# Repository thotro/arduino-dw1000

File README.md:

# arduino-dw1000

A library that offers basic functionality to use Decawave's DW1000 chips/modules with Arduino
(see https://www.decawave.com/products/dwm1000-module).

Project state
-------------

**Development:**
There is **no active development** by the owner *thotro*.

This library is currently (2019) **not actively maintained**.

Anyway you can create pull requests if you found a bug or developed a new feature. They maybe help others.

**TODOs:**
* Fill wiki: https://github.com/thotro/arduino-dw1000/wiki
* MAC and frame filtering, error handling
* Sleep/power optimizations
* Refactor `DW1000Mac`
* Refactor `DW1000Ranging`
* Refactor `DW1000Device`
* Update examples (complete todos in header notice)

**What can I do with this lib?:**
Stable transmission of messages between two modules is possible. The code for device tuning is working as well, hence different modes of operation can be chosen. As frame filtering (i.e. via MAC conforming messages) is partially implemented yet, internal features of the chip for node addressing and auto-acknowledgement of messages can not be used. This is part of a future milestone. For now, if acknowledgements are required, they have to be sent manually and node addresses have to be encoded in the message payload and processed by the host controller.

**General notice:**
* The documentation https://github.com/thotro/arduino-dw1000/tree/master/extras/doc is manually generated and maybe out of date.
* Datasheet and application notices are available at https://www.decawave.com/ (require free registration).

Installation
------------

**Requires c++11 support**, Arduino IDE >= 1.6.6 support c++11.

 1. Get a ZIP file of the master branch or the latest release and save somewhere on your machine.
 2. Open your Arduino IDE and goto _Sketch_ / _Include Library_ / _Add .ZIP Library..._
 3. Select the downloaded ZIP file of the DW1000 library
 4. You should now see the library in the list and have access to the examples in the dedicated section of the IDE

Note that in version 1.6.6 of your Arduino IDE you can get the library via the Arduino library manager.

Contents
--------

 * [Project structure](../../wiki/Project-structure)
 * [Features and design intentions](../../wiki/Features)
 * [Testbed and Adapter board](../../wiki/Testbed-and-Adapter-board)
 * [Projects, Media, Links](../../wiki/Projects)
 * [Benchmarks](../../wiki/Benchmarks)
 * API docs
   * [HTML](https://cdn.rawgit.com/thotro/arduino-dw1000/master/extras/doc/html/index.html)
   * [PDF](https://cdn.rawgit.com/thotro/arduino-dw1000/master/extras/doc/DW1000_Arduino_API_doc.pdf)

Usage
-----

General usage of the DW1000 library is depicted below. Please see the Arduino test example codes (described in the [project structure](../../wiki/Project-structure)) for more up-to-date and operational reference usage. 

At the moment the library contains two types:
 * **DW1000:**
 State: stable.
 The statically accessible entity to work with your modules. Offers a variety of configuration options and manages module states and actions. 
 
 * **DW1000Time:**
 State: stable.
 Container entities that handle DW1000 specific timing values. These are required to allow accurate timestamps and time based computations; they aid in avoiding potential precision and capacity problems of standard number formats in Arduino and basically are wrapper objects for 64-bit signed integer data types; most importantly they take care of all bit-to-time-and-distance (and vice versa) conversions.
 
 * **DW1000Ranging:**
 State: prototype.
 Contain all functions which allow to make the ranging protocole. 
 
 * **DW1000Device:**
 State: prototype.
 Contain all informations (long address, short ephemeral address, DW1000Time of transition)  about a distant device (anchor or tag) on the same network.
 
 * **DW1000Mac:**
 State: prototype.
 This class is a child of the DW1000Device class and allow to generate the MAC frame for his DW1000Device parent.

```Arduino
#include <DW1000.h>
...
// init with interrupt line and optionally with reset line
DW1000.begin(irq_pin[, rst_pin]);
// select a specific chip via a chip select line
DW1000.select(cs_pin);
// or use DW1000.reselect(cs_pin) to switch to previously selected chip
...
// open a device configuration sessions
DW1000.newConfiguration();
// configure specific aspects and/or choose defaults
DW1000.setDefaults();
DW1000.setDeviceAddress(5);
DW1000.setNetworkId(10);
// modes that define data rate, frequency, etc. (see API docs)
DW1000.enableMode(DW1000.MODE_LONGDATA_RANGE_LOWPOWER);
// ... and other stuff - finally upload to the module.
DW1000.commitConfiguration();
...
// set some interrupt callback routines
DW1000.attachSentHandler(some_handler_function);
DW1000.attachReceivedHandler(another_handler_function);
...
// open a new transmit session
DW1000.newTransmit();
// configure specific aspects and/or choose defaults
DW1000.setDefaults();
DW1000.setData(some_data);
DW1000Time delayTime = DW1000Time(100, DW1000Time::MILLISECONDS);
[DW1000Time futureTimestamp = ]DW1000.setDelay(delayTime);
// ... and other stuff - finally start the transmission
DW1000.startTransmit();
...
// similar for a receiving session, like so ...
DW1000.newReceive();
DW1000.setDefaults();
// so we don't need to restart the receiver manually each time
DW1000.receivePermanently(true);
// ... and other stuff - finally start awaiting messages
DW1000.startReceive();
...
```

Dependency
----------

Disclaimer:
This is maybe a incomplete list. Please notice that some dependency libraries may **require** a **reproduction** of copyright and license, **even if they are shipped as binary!!**

* **Arduino.h**

  * From: Arduino IDE / target specific
  * License: (target: Arduino) GNU Lesser General Public License 2.1
  
* **SPI.h**

  * From: Arduino IDE / target specific
  * License: (target: Arduino) GNU Lesser General Public License 2.1
  
* **stdint.h**

  * From: Arduino IDE / Compiler and target specific
  * License: different

* **stdio.h**

  * From: Arduino IDE / Compiler and target specific
  * License: different
  
* **stdlib.h**

  * From: Arduino IDE / Compiler and target specific
  * License: different
  
* **string.h**

  * From: Arduino IDE / Compiler and target specific
  * License: different

License
-------
Apache License 2.0 (see [LICENSE.md](https://github.com/thotro/arduino-dw1000/blob/master/LICENSE.md))

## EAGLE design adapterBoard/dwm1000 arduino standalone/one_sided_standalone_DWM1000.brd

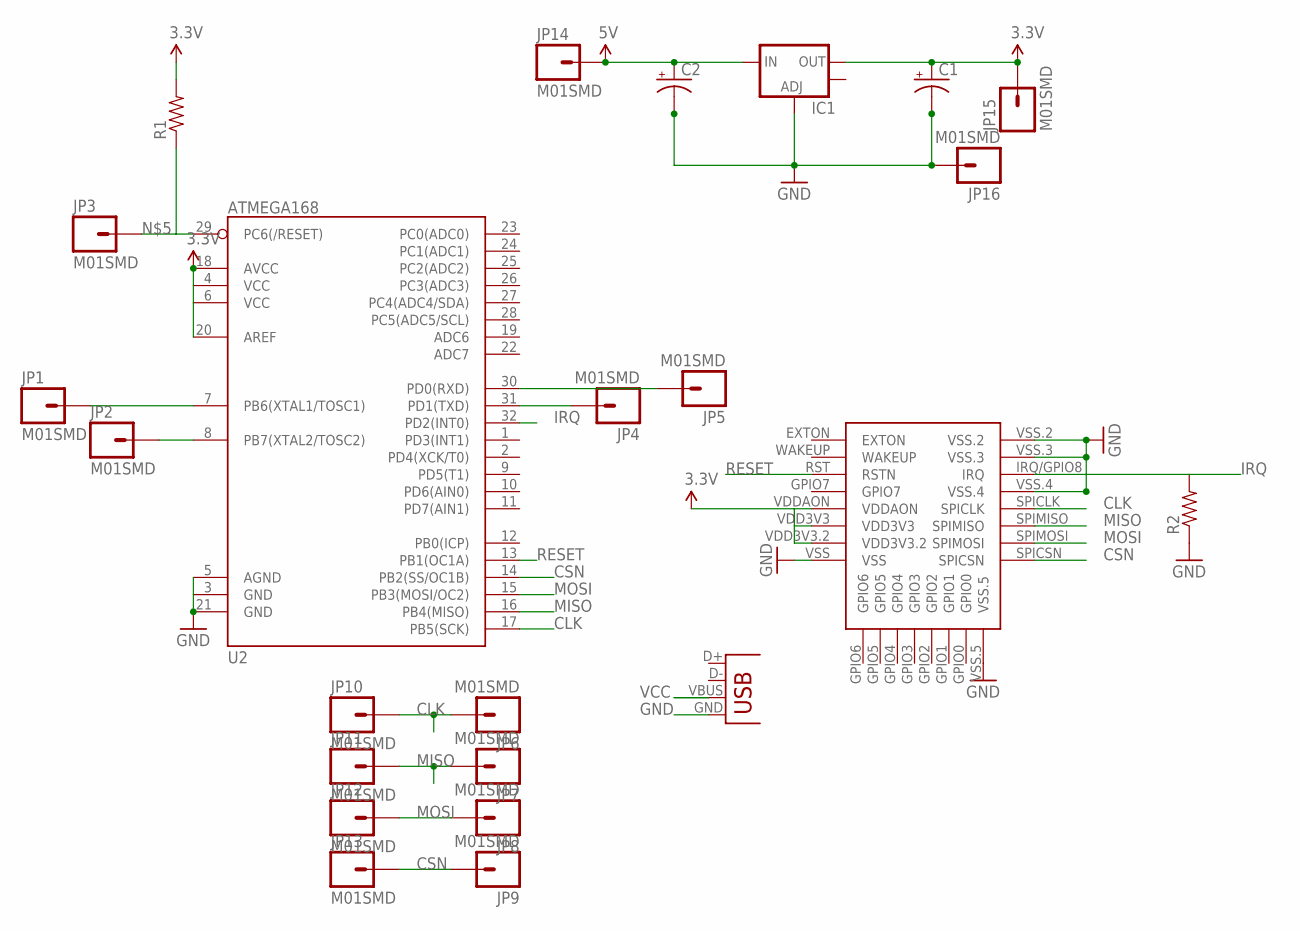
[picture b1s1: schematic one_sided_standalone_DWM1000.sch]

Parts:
C1, C2: CAP_POL3528-KIT; EIA3528-KIT
IC1: V_REG_LM1117SOT223; SOT223
JP1, JP2, JP3, JP4, JP5, JP6, JP7, JP8, JP9, JP10, JP11, JP12, JP13, JP14, JP15, JP16: M01SMD; LUXEON-PAD
R1, R2: RESISTOR0805-RES; 0805
U2: ATMEGA168; TQFP32-08
U$1: DWM1000
X1: USB-MICROB

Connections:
CLK: JP6.P$1, JP10.P$1, U2.17 (PB5(SCK)), U$1.SPICLK
CSN: JP9.P$1, JP13.P$1, U2.14 (PB2(SS/OC1B)), U$1.SPICSN
GND: C1.C (-), C2.C (-), IC1.1 (ADJ), JP16.P$1, R2.1, U2.3 (GND), U2.5 (AGND), U2.21 (GND), U$1.VSS, U$1.VSS.2, U$1.VSS.3, U$1.VSS.4, U$1.VSS.5, X1.GND
IRQ: R2.2, U2.32 (PD2(INT0)), U$1.IRQ/GPIO8 (IRQ)
MISO: JP7.P$1, JP11.P$1, U2.16 (PB4(MISO)), U$1.SPIMISO
MOSI: JP8.P$1, JP12.P$1, U2.15 (PB3(MOSI/OC2)), U$1.SPIMOSI
unnamed: JP1.P$1, U2.7 (PB6(XTAL1/TOSC1))
unnamed: JP2.P$1, U2.8 (PB7(XTAL2/TOSC2))
unnamed: JP3.P$1, R1.1, U2.29 (PC6(/RESET))
unnamed: JP4.P$1, U2.31 (PD1(TXD))
unnamed: JP5.P$1, U2.30 (PD0(RXD))
RESET: U2.13 (PB1(OC1A)), U$1.RST (RSTN)
VCC: C2.A (+), IC1.3 (IN), JP14.P$1, X1.VBUS
VCC3.3: C1.A (+), IC1.2 (OUT), JP15.P$1, R1.2, U2.6 (VCC), U2.18 (AVCC), U2.20 (AREF), U$1.VDD3V3, U$1.VDD3V3.2, U$1.VDDAON

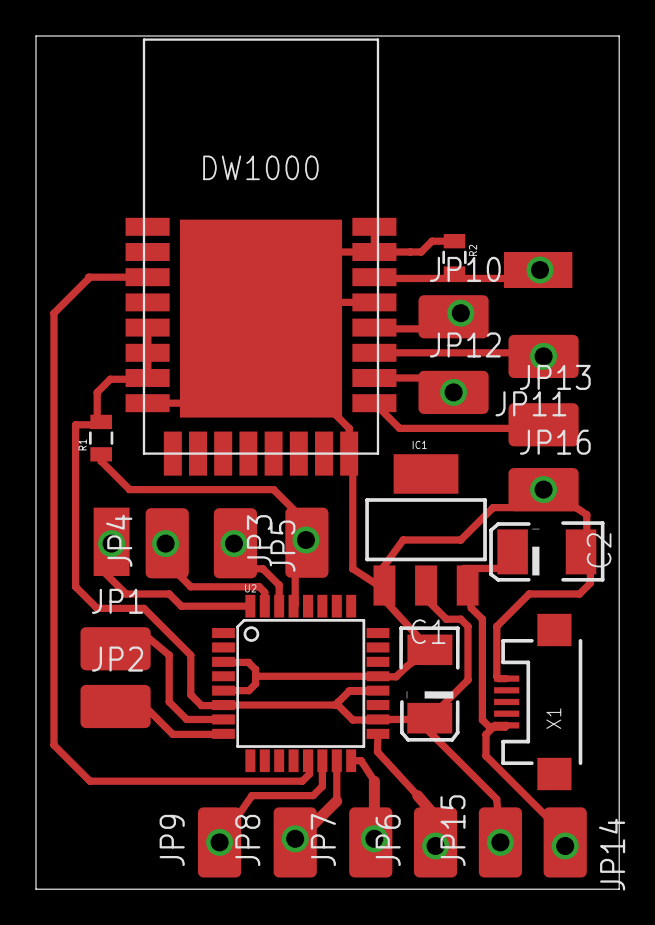
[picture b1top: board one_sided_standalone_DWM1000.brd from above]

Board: 2 copper layers, 32.4 x 47.4 mm, 24 parts (0 on the bottom side), 14 nets.

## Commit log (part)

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2015-01-22 initial arduino test code
2015-01-24 some further commands used arduino.h bit handling
2015-01-25 TX related registers, especially TX_FCTRL
2015-01-26 DEBUG/Unit code, unit test project initial commit
2015-01-26 project structure explained
2015-02-05 capture most important RX system status events
2015-02-08 adapter board for 0.1in breadboard/protoboard (first draft)
2015-03-06 first production version of adapter board
2015-04-12 pretty bit field printing, bug fixes
2015-04-15 interrupt handling, chip reset and fixes
2015-04-18 mem optimization, RX/TX tests (in progress)
2015-04-19 pretty register content printing (device debug)
2015-04-20 default configuration fixes according to spec
2015-05-17 bugfix, internal channel control and device tuning
2015-05-18 device configuration tuning
2015-05-20 Simple (Arduino-)String based RX/TX data handling
2015-05-21 stable RX/TX, bugfix mem leak
2015-05-23 Testbed description
2015-05-27 Refactored to single static object (DW1000) + infrastructure for callback handlers
2015-05-31 stability fixes + more RX callbacks
2015-06-01 Updated info
2015-06-08 ranging demo (in progress)
2015-06-13 Timestamp bugfix + first ranging results (still require testing)
2015-06-15 code cleanup
2015-06-16 soft reset + tuning code completed + bugfix in syscfg
2015-06-19 fixed wiki links
2015-06-19 fixed ping pong test
2015-06-20 minor fix and readme update
2015-06-24 bugfix chip tuning
2015-06-25 OTP and calibration (in progress)
2015-06-25 api doc (in progress), api cleanup + bugfix for tune
2015-06-26 exclude doc from stats
2015-06-30 Fixed returned future time in setDelay(..) (antenna delay compensation)
2015-07-03 device mode printing + some progress on ranging
2015-07-04 progress on API docs
2015-07-06 changed to more permissive Apache License + Arduino conforming library format (1.5)
2015-07-06 specified and tagged v0.5, as Arduino conforming library
2015-07-06 bugfix SPI, enableClock order (thanks Ankit)
2015-07-07 bugfix preamble code + first path signal strength read-back
2015-07-07 fixed broken links to API docs
2015-07-14 Gerber files for adapter board
2015-07-17 receive power level + dBm correction
2015-07-18 smart tx power management
2015-07-21 bugfix in 110kbps tuning
2015-07-25 Apache license for all examples
2015-07-31 allow shorter replyDelay
    - decreasing the waiting time after readBytes or writeBytes
    - digitalWriteFast for ss pin
2015-07-31 timestamp correction in ranging example + ranging Hz debug printing
2015-08-01 adding eagle files
2015-08-01 add of pdf etch for arduino standalone + dwm1000
2015-08-03 Adding all datasheets and application note for DW1000
2015-08-04 lang stats update
2015-08-04 removed datasheets for smaller lib size
2015-08-05 Adding of DW1000Device
    The structure allow to have multiples devices. We now just need to add
    the mac frame !
2015-08-06 Auto RX timestamp correction
2015-08-06 automatic RX timestamp correction (in-progress)
2015-08-07 range bias correction on each RX stamp
2015-08-09 mac layer is working but error in ranging
    ranging not working in this branch…
    But mac layer/filtering is working great :D
    Can’t find the problem…
2015-08-09 DW1000Ranging with mac layer
    First sketch for mac layer ! I tried to comment a lot, i hope it will
    be good for you :-)
    There is still optimisation to do on it !
2015-08-09 Update DW1000Ranging_TAG
    correction when showing shortAddress (adding HEX)
2015-08-10 bugfix range bias correction
2015-08-10 missing file
2015-08-12 POLL sent with same frequence
    The poll is sent each 45ms
    -> allow to avoid the time we loose with reset inactive.
    -> the anchor still keep the reset inactive but with a very shorter
    delay
2015-08-12 multiple anchors part. 1
    - tag manage its anchors. It can delete them if they are inactive (2s)
    or adding them when receive ranging_init message.
    - tested with 3 devices.
    ->next to do: broadcast message for poll and range message with datas
    (times or replyTimeDelay) for each active anchors
2015-09-16 variable naming collision on STM32
2015-09-18 Fixed issue #36: wrong extended address bit on readBytes
2016-02-04 added projects/media link
2016-02-04 removed dead links
2016-02-05 Refactoring + Overloads For init & StartAs*
    - Added Overload For initCommunication To Allow Passing In Interrupt
    (Note: This is the actual interrupt, not the physical pin)
    - Added Overloads For StartAsAnchor & StartAsTag To Allow Passing In
    FamilyID, NodeID, and NetworkID
    - Refactored StartAsAnchor & StartAsTag To Accomodate Overloads
    - Refactored & Consolidated Overloads For AddNewworkDevices
2016-04-05 add travis
2016-05-04 code style of all files equal
    - done with clion
    - makes it easier to refactor code
2016-05-07 fix debug msg buffer length
    most examples had wrong size
    documentation says 128 bytes
2016-05-11 Changed all message buffers in example code to 128 bytes. This is the largest value needed for function returns. Now consistent accross example files
2016-05-26 update examples
    - add pin configuration to beginning
    - move some strings to flash
2016-06-01 fix digitalWriteFast only for AVR
    fixes #84
2016-06-03 change reset pin rst behaviour
    Changes to the hardware reset sequence : according to the DW1000 data
    sheet §5.6.1 page 20, the RSTn pin should not be driven high but left
    floating.
    Source: @tommag committed on 23 Mar 16
2016-06-04 add irq to dw1000ranging
    as suggested in #82
2016-06-05 disable frame filter by default, change setting public to change
    as suggested by comments to 9e135eabd32cb09268b0a30f793913fe88ee1cc9
2016-06-10 Initialize replyTime to 0. On 32bit systems, this could cause a random value for the 2 high bytes, resulting in really high delay values and an unusable system.
2016-06-20 Added distance filter for DW1000Ranging (TAG and ANCHOR)
2016-06-21 Fixed indentation
2016-06-23 Added handlers on blink (ANCHOR), range init (TAG) and inactive (ANCHOR, TAG) events
2016-07-09 fix example
    - MessagePingPong used wrong var msg instead of msgInfo
    - improve: enum instead of preprocessor
2016-07-15 refactored DW1000Time - DW1000Time now printable - costs more ram and rom so optional deactivate it by new DW1000CompileOptions.h - deprecated getAsFloat and print - replace getAsFloat with getAsMicr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
2016-08-04 Cleanup: silent some compilation warnings, fix comments, use FC_1_BLINK define.
    This commit silents some compilation warnings:
    DW1000Mac.cpp: In member function ‘int DW1000Mac::decodeShortMACFrame(uint8_t*, uint8_t*)’:
    DW1000Mac.cpp:132:1: warning: no return statement in function returning non-void [-Wreturn-type]
    DW1000Mac.cpp: In member function ‘int DW1000Mac::decodeLongMACFrame(uint8_t*, uint8_t*)’:
    DW1000Mac.cpp:141:1: warning: no return statement in function returning non-void [-Wreturn-type]
    DW1000Ranging.cpp: In static member function ‘static short int DW1000RangingClass::detectMessageType(uint8_t*)’:
2016-08-04 Don't set USR_SFD register twice during init.
    enableMode() is usually called twice, once from
    DW1000Class::setDefaults(), second time explicit by application.
    This makes USR_SFD register set twice during init.
    Move setting register it to DW1000Class::commitConfiguration()
2016-08-28 changing short to int as suggested by @Rotzbua
2016-10-21 move preprocessor constants to extra file
    rm double def of preprocessor constants
2016-10-21 remove digitalWriteFast
    as suggested in #89 digitalwrite is faster in newer ide (>=1.6)
    fixes #40
2016-10-22 fixed integers for DW1000Mac
2016-10-22 fixed integers for DW1000Ranging
2016-10-22 fixed integers for DW1000
2016-10-25 update temp and vbat function
2016-10-25 fix sub register
    subregister 0x00 and NO_SUB were equal -> changed value of NO_SUB
2016-10-30 fix forgotten int
    change to fixed sized int -> stdint.h
2016-10-30 fix bug reset pin and soft reset
    reset pin value -1 was soft reset but never triggert because reset pin
    variable was unsigned
2016-12-20 Updated documentation to the current master (Dec 20 2016) Changed docxygen config from C to C++ and html to compressed html.
2016-12-30 add support for GPIO led blinking
2017-01-28 Fixed tuning (FS_PLL) for channels 5 and 7 Thanks to 'gabrielortiz616'.
2017-02-05 replaces spaces with tabs
2017-02-13 preserve pmscctrl0[1] on lde load
2017-04-05 Update DW1000.cpp
    Bug in clearAllStatus()- previous implementation has writing a value of 0 to every bit in the status register, while per the user manual latched bits in sys_status are cleared by writing 1 to them. c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
    When I tested the previous version of clearAllStatus() it resulted in no change to the internal status register of the DW1000 (which can be read by calling readSystemEventStatusRegister()). On the ot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
2017-04-19 Updated isReceiveTimeout() to check for Preamble and SFD timeout as well
    isReceiveTimeout() currently only checks to see if RXRFTO is high, but there are two other potential timeout flags-- the RX SFD timeout is enabled by default and the RX Preamble timeout can be enable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
    Will make separate pull request to include #defines for RXPTO_BIT and RXSFDTO_BIT (21 and 26, respectively)
2017-04-19 missing semicolon after edits for and RXSFDTO and RXPTO in isReceiveTimeout()
2017-04-19 Added comments describing updated functionality
2017-04-21 Update README.md
    upd actual state of the project
2017-05-14 Update DW1000.cpp
    While using the library with an ESP12e, the SPI clock has to be changed to 20 MHz as 16 Mhz can not be generated while running with 80 MHz.
2017-05-14 Update DW1000.cpp
    For ESP8266, the irq must be forced to be an input manually, see https://github.com/thotro/arduino-dw1000/issues/132.
2017-05-18 Just code style
2017-07-09 fix third anchor loosing connection
    This bug is reported in several issues (#116, #179). Some solutions have
    been implemented like here:
    https://github.com/ybc82/arduino-dw1000/commit/22d215eeb3ebf800b5df9a5dea8f82ec601283cd
    This pull request have been succesfully tested with 3 anchors and 1 tag.
2017-07-09 add option to set anchors static short addresses
    The first two bytes of the full address can be used as static short
    address. By default, the previous behavior (random address) is used.
2017-08-15 Changed the sign of the timestamp correction, changed constants related to signal power computations, and changed some < and > operators to <= and >= in correctTimestamp function to fix an inconsiste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
2017-10-04 Update README.md
    add license to readme
2017-10-07 Update README.md
    add fancy badges
2017-11-23 Inital commit for the antenna delay calibration.
2018-03-20 Fix value of FS_PLLTUNE for channel 3 in DW1000Class::tune
2018-04-07 replace NULL by nullptr
2018-07-07 fix code highlighting
2018-07-15 Use a single tab field separator in keywords.txt
    Each field of keywords.txt is separated by a single true tab. When you use multiple tabs it causes the field to be interpreted as empty. On Arduino IDE 1.6.5 and newer an empty KEYWORD_TOKENTYPE caus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
    Reference:
    https://github.com/arduino/Arduino/wiki/Arduino-IDE-1.5:-Library-specification#keywords
2018-07-26 Improved commitConfiguration function
2018-07-26 Add code for retro-compatibility
2018-07-27 Add operation modes based on DW1000 manual
2018-07-29 Fixed error in the precedent commit
    forgot square parentheses in arrays of modes
2018-08-01 Converted if statement to switch.
2018-08-01 Shortened setDefaults code
2018-08-01 Moved default channel setting inside setDefaults
2018-08-02 Fixed sfd sequence configuration for 110Kbps Co-authored-by: Sonic0 <andrea.salvatori92@gmail.com>
2018-08-02 Automatically set of Preamble Code when setting Channel manually
2018-10-11 Add dependency/license documentation
    ref #290
2018-10-11 fix format
    fix 80de2a2bd2eef49d95e3f743048f9e7a01aa86b9
2019-06-12 [doc] inactive maintenance
2019-06-12 bump to version 0.8
2019-06-12 bump version to 0.9
2019-06-26 Fix Overflow on Temp & VBat
    If not cast to float first the computed values become irregular,
    like (temp, vbat) = (-108.099991, 2.317341).
    After this revision and validation by thermometer, the values are
    reasonable (62.899998, 3.184393).
2019-07-18 Added header guard
2019-07-20 CHANNEL in DW1000 Ragniging
2020-05-11 add license
2023-10-17 Added Support for ESP32
    SPI.usingInterrupt() is not available on ESP32 as well as ESP8266. Extended checking for the preprocesser marco to include the ESP32.
2024-01-16 numberDevices in loop to uint16_t
2024-01-16 Disabled printable

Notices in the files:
README.md:
License: Apache 2
parts and their libraries:
SparkFun: Licensing: CC v3.0 Share-Alike You are welcome to use this library for commercial purposes.
